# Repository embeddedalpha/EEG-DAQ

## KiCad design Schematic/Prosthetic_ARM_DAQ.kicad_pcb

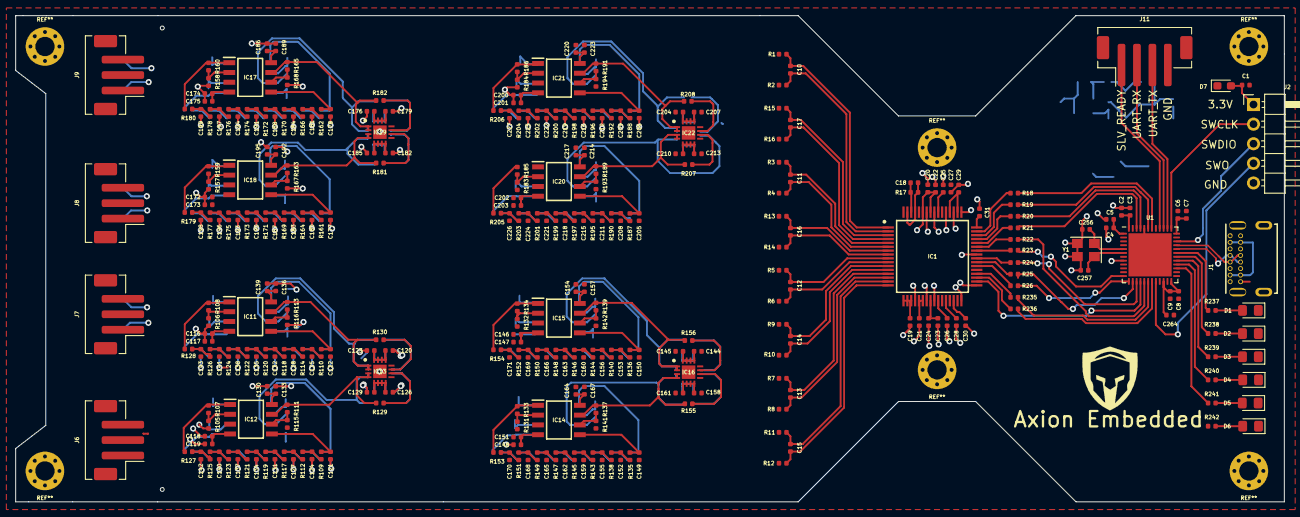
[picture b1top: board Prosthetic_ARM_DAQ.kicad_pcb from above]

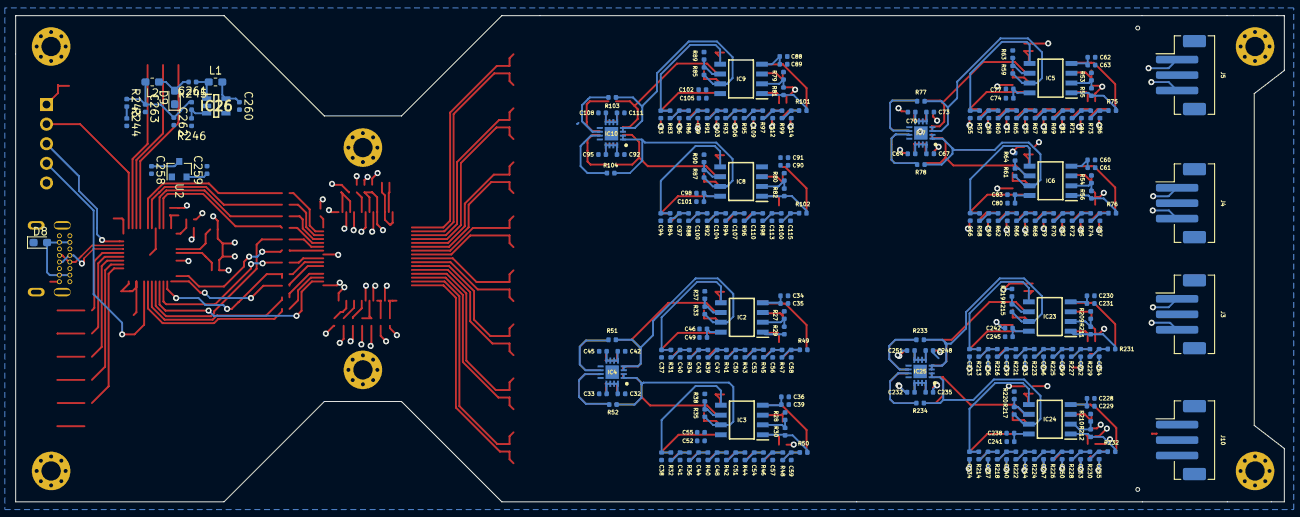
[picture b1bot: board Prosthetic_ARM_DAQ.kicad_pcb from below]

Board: 4 copper layers, 164.4 x 63.0 mm, 561 parts (248 on the bottom side), 301 nets.

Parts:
C1, C2, C4, C6, C8, C258, C259, C260, C261, C262, C263: 100U; C_0402_1005Metric
C3, C5, C7, C9, C256, C257, C264: 1N; C_0402_1005Metric
C10, C11, C12, C13, C14, C15, C16, C17, C37, C38, C40, C41, C43, C44, C47, C48, C50, C51, C53, C54, C56, C57, C58, C59, C65, C66, C68, C69, C71, C72, C75, C76, C78, C79, C81, C82, C84, C85, C86, C87, C93, C94, C96, C97, C99, C100, C103, C104, C106, C107, C109, C110, C112, C113, C114, C115, C121, C122, C124, C125, C127, C128, C131, C132, C134, C135, C137, C138, C140, C141, C142, C143, C149, C150, C152, C153, C155, C156, C159, C160, C162, C163, C165, C166, C168, C169, C170, C171, C177, C178, C180, C181, C183, C184, C187, C188, C190, C191, C193, C194, C196, C197, C198, C199, C205, C206, C208, C209, C211, C212, C215, C216, C218, C219, C221, C222, C224, C225, C226, C227, C233, C234, C236, C237, C239, C240, C243, C244, C246, C247, C249, C250, C252, C253, C254, C255: C_Small; C_0402_1005Metric
C18, C19, C20, C21, C22, C23, C24, C25, C26, C27, C28, C29, C30, C31: 1U; C_0402_1005Metric
C32, C34, C36, C42, C46, C52, C60, C62, C64, C70, C74, C80, C88, C90, C92, C98, C102, C108, C116, C118, C120, C126, C130, C136, C144, C146, C148, C154, C158, C164, C172, C174, C176, C182, C186, C192, C200, C202, C204, C210, C214, C220, C228, C230, C232, C238, C242, C248: 0.1U; C_0402_1005Metric
C33, C35, C39, C45, C49, C55, C61, C63, C67, C73, C77, C83, C89, C91, C95, C101, C105, C111, C117, C119, C123, C129, C133, C139, C145, C147, C151, C157, C161, C167, C173, C175, C179, C185, C189, C195, C201, C203, C207, C213, C217, C223, C229, C231, C235, C241, C245, C251: 10U; C_0402_1005Metric
D1, D2, D3, D4, D5, D6: LED; LED_0805_2012Metric_Pad1.15x1.40mm_HandSolder
D7, D8, D9: D_Small; D_0603_1608Metric_Pad1.05x0.95mm_HandSolder
IC1: ADS1299-4PAGR; QFP50P1200X1200X120-64N
IC2, IC3, IC5, IC6, IC8, IC9, IC11, IC12, IC14, IC15, IC17, IC18, IC20, IC21, IC23, IC24: ADA4075-2ARZ; SOIC127P600X175-8N
IC4, IC7, IC10, IC13, IC16, IC19, IC22, IC25: AD8476ACPZ-WP; QFN50P300X300X80-17N-D
IC26: LM2611AMF; SOT95P280X145-5N
J1: USB4085-GF-A_REVA; USB_C_New
J2: Conn_01x05; PinHeader_1x05_P2.54mm_Horizontal
J3, J4, J5, J6, J7, J8, J9, J10: Conn_01x03; JST_PH_B3B-PH-SM4-TB_1x03-1MP_P2.00mm_Vertical
J11: Conn_01x04; JST_PH_B4B-PH-SM4-TB_1x04-1MP_P2.00mm_Vertical
L1, L2: L_Small; L_0603_1608Metric_Pad1.05x0.95mm_HandSolder
R1, R2, R3, R4, R5, R6, R7, R8, R9, R10, R11, R12, R13, R14, R15, R16, R17, R18, R19, R20, R21, R22, R23, R24, R25, R26, R27, R28, R29, R30, R31, R32, R33, R34, R35, R36, R37, R38, R39, R40, R41, R42, R43, R44, R45, R46, R47, R48, R49, R50, R51, R52, R53, R54, R55, R56, R57, R58, R59, R60, R61, R62, R63, R64, R65, R66, R67, R68, R69, R70, R71, R72, R73, R74, R75, R76, R77, R78, R79, R80, R81, R82, R83, R84, R85, R86, R87, R88, R89, R90, R91, R92, R93, R94, R95, R96, R97, R98, R99, R100, R101, R102, R103, R104, R105, R106, R107, R108, R109, R110, R111, R112, R113, R114, R115, R116, R117, R118, R119, R120, R121, R122, R123, R124, R125, R126, R127, R128, R129, R130, R131, R132, R133, R134, R135, R136, R137, R138, R139, R140, R141, R142, R143, R144, R145, R146, R147, R148, R149, R150, R151, R152, R153, R154, R155, R156, R157, R158, R159, R160, R161, R162, R163, R164, R165, R166, R167, R168, R169, R170, R171, R172, R173, R174, R175, R176, R177, R178, R179, R180, R181, R182, R183, R184, R185, R186, R187, R188, R189, R190, R191, R192, R193, R194, R195, R196, R197, R198, R199, R200, R201, R202, R203, R204, R205, R206, R207, R208, R209, R210, R211, R212, R213, R214, R215, R216, R217, R218, R219, R220, R221, R222, R223, R224, R225, R226, R227, R228, R229, R230, R231, R232, R233, R234, R235, R236, R237, R238, R239, R240, R241, R242, R243, R244, R245, R246: R_Small; R_0402_1005Metric
U1: STM32F411CEUx; QFN-48-1EP_7x7mm_P0.5mm_EP5.6x5.6mm
U2: AP2127N-3.3; SOT-23
Y1: Crystal_GND23; Crystal_SMD_TXC_7M-4Pin_3.2x2.5mm

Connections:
+3V3: C2.1, C3.1, C4.1, C5.1, C6.1, C7.1, C8.1, C9.1, C19.1, C20.1, C21.2, C22.1, C27.1, C29.2, C31.1, C42.1, C45.1, C46.1, C49.1, C52.1, C55.1, C70.1, C73.1, C74.1, C77.1, C80.1, C83.1, C98.1, C101.1, C102.1, C105.1, C108.1, C111.1, C126.1, C129.1, C130.1, C133.1, C136.1, C139.1, C154.1, C157.1, C158.1, C161.1, C164.1, C167.1, C182.1, C185.1, C186.1, C189.1, C192.1, C195.1, C210.1, C213.1, C214.1, C217.1, C220.1, C223.1, C238.1, C241.1, C242.1, C245.1, C248.1, C251.1, C259.1, C264.2, IC1.17, IC1.18, IC1.19, IC1.21, IC1.22, IC1.48, IC1.50, IC1.52, IC1.54, IC1.57, IC1.59, IC2.8, IC3.8, IC4.5, IC4.6, IC4.7, IC4.8, IC5.8, IC6.8, IC7.5, IC7.6, IC7.7, IC7.8, IC8.8, IC9.8, IC10.5, IC10.6, IC10.7, IC10.8, IC11.8, IC12.8, IC13.5, IC13.6, IC13.7, IC13.8, IC14.8, IC15.8, IC16.5, IC16.6, IC16.7, IC16.8, IC17.8, IC18.8, IC19.5, IC19.6, IC19.7, IC19.8, IC20.8, IC21.8, IC22.5, IC22.6, IC22.7, IC22.8, IC23.8, IC24.8, IC25.5, IC25.6, IC25.7, IC25.8, R242.1, U1.1, U1.7, U1.9, U1.22, U1.24, U1.36, U1.48, U2.2
-3V3: C32.1, C33.1, C34.1, C35.1, C36.1, C39.1, C60.1, C61.1, C62.1, C63.1, C64.1, C67.1, C88.1, C89.1, C90.1, C91.1, C92.1, C95.1, C116.1, C117.1, C118.1, C119.1, C120.1, C123.1, C144.1, C145.1, C146.1, C147.1, C148.1, C151.1, C172.1, C173.1, C174.1, C175.1, C176.1, C179.1, C200.1, C201.1, C202.1, C203.1, C204.1, C207.1, C228.1, C229.1, C230.1, C231.1, C232.1, C235.1, IC2.4, IC3.4, IC4.13, IC4.14, IC4.15, IC4.16, IC5.4, IC6.4, IC7.13, IC7.14, IC7.15, IC7.16, IC8.4, IC9.4, IC10.13, IC10.14, IC10.15, IC10.16, IC11.4, IC12.4, IC13.13, IC13.14, IC13.15, IC13.16, IC14.4, IC15.4, IC16.13, IC16.14, IC16.15, IC16.16, IC17.4, IC18.4, IC19.13, IC19.14, IC19.15, IC19.16, IC20.4, IC21.4, IC22.13, IC22.14, IC22.15, IC22.16, IC23.4, IC24.4, IC25.13, IC25.14, IC25.15, IC25.16, R243.2, R244.1
/Analog_AFE/sheet5F407F6A/EMG1_+: IC13.10, R12.1, R129.1
/Analog_AFE/sheet5F407F6A/EMG1_-: IC13.11, R11.2, R130.1
/Analog_AFE/sheet5F407F6A/IN1: IC12.7, IC13.3, IC13.4, R111.1, R129.2
/Analog_AFE/sheet5F407F6A/IN2: IC11.7, IC13.1, IC13.2, R113.1, R130.2
/Analog_AFE/sheet5F407F6B/EMG2_+: IC16.10, R10.1, R155.1
/Analog_AFE/sheet5F407F6B/EMG2_-: IC16.11, R9.2, R156.1
/Analog_AFE/sheet5F407F6B/IN1: IC14.7, IC16.3, IC16.4, R137.1, R155.2
/Analog_AFE/sheet5F407F6B/IN2: IC15.7, IC16.1, IC16.2, R139.1, R156.2
/Analog_AFE/sheet5F407F6C/EMG3_+: IC19.10, R14.1, R181.1
/Analog_AFE/sheet5F407F6C/EMG3_-: IC19.11, R13.2, R182.1
/Analog_AFE/sheet5F407F6C/IN1: IC18.7, IC19.3, IC19.4, R163.1, R181.2
/Analog_AFE/sheet5F407F6C/IN2: IC17.7, IC19.1, IC19.2, R165.1, R182.2
/Analog_AFE/sheet5F407F6D/EMG4_+: IC22.10, R16.1, R207.1
/Analog_AFE/sheet5F407F6D/EMG4_-: IC22.11, R15.2, R208.1
/Analog_AFE/sheet5F407F6D/IN1: IC20.7, IC22.3, IC22.4, R189.1, R207.2
/Analog_AFE/sheet5F407F6D/IN2: IC21.7, IC22.1, IC22.2, R191.1, R208.2
/Analog_AFE/sheet5F407F6E/EEG1_+: IC25.10, R8.1, R233.1
/Analog_AFE/sheet5F407F6E/EEG1_-: IC25.11, R7.2, R234.1
/Analog_AFE/sheet5F407F6E/IN1: IC23.7, IC25.3, IC25.4, R215.1, R233.2
/Analog_AFE/sheet5F407F6E/IN2: IC24.7, IC25.1, IC25.2, R217.1, R234.2
/Analog_AFE/sheet5F407F67/EEG2_+: IC4.10, R6.1, R51.1
/Analog_AFE/sheet5F407F67/EEG2_-: IC4.11, R5.2, R52.1
/Analog_AFE/sheet5F407F67/IN1: IC2.7, IC4.3, IC4.4, R33.1, R51.2
/Analog_AFE/sheet5F407F67/IN2: IC3.7, IC4.1, IC4.2, R35.1, R52.2
/Analog_AFE/sheet5F407F68/EEG3_+: IC7.10, R4.1, R77.1
/Analog_AFE/sheet5F407F68/EEG3_-: IC7.11, R3.2, R78.1
/Analog_AFE/sheet5F407F68/IN1: IC5.7, IC7.3, IC7.4, R59.1, R77.2
/Analog_AFE/sheet5F407F68/IN2: IC6.7, IC7.1, IC7.2, R61.1, R78.2
/Analog_AFE/sheet5F407F69/EEG4_+: IC10.10, R2.1, R103.1
/Analog_AFE/sheet5F407F69/EEG4_-: IC10.11, R1.2, R104.1
/Analog_AFE/sheet5F407F69/IN1: IC9.7, IC10.3, IC10.4, R85.1, R103.2
/Analog_AFE/sheet5F407F69/IN2: IC8.7, IC10.1, IC10.2, R87.1, R104.2
DIN: IC1.34, U1.16
DN_N: J1.A7, J1.B7, U1.32
DN_P: J1.A6, J1.B6, U1.33
DOUT: R22.1, U1.17
DRDY: R18.1, U1.42
GND: C1.2, C2.2, C3.2, C4.2, C5.2, C6.2, C7.2, C8.2, C9.2, C19.2, C20.2, C21.1, C22.2, C23.1, C24.1, C25.1, C26.1, C27.2, C28.1, C29.1, C30.1, C31.2, C32.2, C33.2, C34.2, C35.2, C36.2, C37.2, C38.2, C39.2, C40.2, C41.2, C42.2, C43.2, C44.2, C45.2, C46.2, C47.2, C48.2, C49.2, C50.2, C51.2, C52.2, C53.2, C54.2, C55.2, C56.2, C57.2, C58.2, C59.2, C60.2, C61.2, C62.2, C63.2, C64.2, C65.2, C66.2, C67.2, C68.2, C69.2, C70.2, C71.2, C72.2, C73.2, C74.2, C75.2, C76.2, C77.2, C78.2, C79.2, C80.2, C81.2, C82.2, C83.2, C84.2, C85.2, C86.2, C87.2, C88.2, C89.2, C90.2, C91.2, C92.2, C93.2, C94.2, C95.2, C96.2, C97.2, C98.2, C99.2, C100.2, C101.2, C102.2, C103.2, C104.2, C105.2, C106.2, C107.2, C108.2, C109.2, C110.2, C111.2, C112.2, C113.2, C114.2, C115.2, C116.2, C117.2, C118.2, C119.2, C120.2, C121.2, C122.2, C123.2, C124.2, C125.2, C126.2, C127.2, C128.2, C129.2, C130.2, C131.2, C132.2, C133.2, C134.2, C135.2, C136.2, C137.2, C138.2, C139.2, C140.2, C141.2, C142.2, C143.2, C144.2, C145.2, C146.2, C147.2, C148.2, C149.2, C150.2, C151.2, C152.2, C153.2, C154.2, C155.2, C156.2, C157.2, C158.2, C159.2, C160.2, C161.2, C162.2, C163.2, C164.2, C165.2, C166.2, C167.2, C168.2, C169.2, C170.2, C171.2, C172.2, C173.2, C174.2, C175.2, C176.2, C177.2, C178.2, C179.2, C180.2, C181.2, C182.2, C183.2, C184.2, C185.2, C186.2, C187.2, C188.2, C189.2, C190.2, C191.2, C192.2, C193.2, C194.2, C195.2, C196.2, C197.2, C198.2, C199.2, C200.2, C201.2, C202.2, C203.2, C204.2, C205.2, C206.2, C207.2, C208.2, C209.2, C210.2, C211.2, C212.2, C213.2, C214.2, C215.2, C216.2, C217.2, C218.2, C219.2, C220.2, C221.2, C222.2, C223.2, C224.2, C225.2, C226.2, C227.2, C228.2, C229.2, C230.2, C231.2, C232.2, C233.2, C234.2, C235.2, C236.2, C237.2, C238.2, C239.2, C240.2, C241.2, C242.2, C243.2, C244.2, C245.2, C246.2, C247.2, C248.2, C249.2, C250.2, C251.2, C252.2, C253.2, C254.2, C255.2, C256.1, C257.2, C258.2, C259.2, C260.2, C263.2, C264.1, D1.1, D2.1, D3.1, D4.1, D5.1, D6.1, D9.1, IC1.20, IC1.23, IC1.25, IC1.32, IC1.33, IC1.41, IC1.49, IC1.51, IC1.53, IC1.56, IC1.58, IC4.17, IC7.17, IC10.17, IC13.17, IC16.17, IC19.17, IC22.17, IC25.17, IC26.2, J1.A1, J1.A12, J1.B1, J1.B12, J1.P1, J1.P2, J1.P3, J1.P4, J2.5, J3.2, J4.2, J5.2, J6.2, J7.2, J8.2, J9.2, J10.2, J11.4, R27.2, R28.2, R37.2, R38.2, R53.2, R54.2, R63.2, R64.2, R79.2, R80.2, R89.2, R90.2, R105.2, R106.2, R115.2, R116.2, R131.2, R132.2, R141.2, R142.2, R157.2, R158.2, R167.2, R168.2, R183.2, R184.2, R193.2, R194.2, R209.2, R210.2, R219.2, R220.2, R244.2, R246.2, U1.8, U1.23, U1.35, U1.44, U1.47, U1.49, U2.1, Y1.2, Y1.3
GPIO1: R23.1, U1.12
GPIO2: R21.1, U1.46
GPIO3: R20.1, U1.45
GPIO4: R19.1, U1.43
LED1: R237.1, U1.31
LED2: R238.1, U1.30
LED3: R239.1, U1.29
LED4: R240.1, U1.28
LED5: R241.1, U1.27
NFB: C262.2, IC26.3, R245.2, R246.1
unnamed: C1.1, D7.2, J2.1
unnamed: C10.1, IC1.1, R1.1
unnamed: C10.2, IC1.2, R2.2
unnamed: C11.1, IC1.5, R3.1
unnamed: C11.2, IC1.6, R4.2
unnamed: C12.1, IC1.9, R5.1
unnamed: C12.2, IC1.10, R6.2
unnamed: C13.1, IC1.13, R7.1
unnamed: C13.2, IC1.14, R8.2
unnamed: C14.1, IC1.11, R9.1
unnamed: C14.2, IC1.12, R10.2
unnamed: C15.1, IC1.15, R11.1
unnamed: C15.2, IC1.16, R12.2
unnamed: C16.1, IC1.7, R13.1
unnamed: C16.2, IC1.8, R14.2
unnamed: C17.1, IC1.3, R15.1
unnamed: C17.2, IC1.4, R16.2
unnamed: C18.1, IC1.62, R17.1
unnamed: C18.2, IC1.61, IC1.63, R17.2
unnamed: C23.2, C24.2, IC1.24
unnamed: C25.2, IC1.55
unnamed: C26.2, IC1.26
unnamed: C28.2, IC1.28
unnamed: C30.2, IC1.30
unnamed: C37.1, IC2.5, R31.1
unnamed: C38.1, IC3.5, R32.1
unnamed: C40.1, R31.2, R34.1
unnamed: C41.1, R32.2, R36.1
unnamed: C43.1, R34.2, R39.1
unnamed: C44.1, R36.2, R40.1
unnamed: C47.1, R39.2, R41.1
unnamed: C48.1, R40.2, R42.1
unnamed: C50.1, R41.2, R43.1
unnamed: C51.1, R42.2, R44.1
unnamed: C53.1, R43.2, R45.1
unnamed: C54.1, R44.2, R46.1
unnamed: C56.1, R45.2, R47.1
unnamed: C57.1, R46.2, R48.1
unnamed: C58.1, R47.2, R49.1
unnamed: C59.1, R48.2, R50.1
unnamed: C65.1, IC5.5, R57.1
unnamed: C66.1, IC6.5, R58.1
unnamed: C68.1, R57.2, R60.1
unnamed: C69.1, R58.2, R62.1
unnamed: C71.1, R60.2, R65.1
unnamed: C72.1, R62.2, R66.1
unnamed: C75.1, R65.2, R67.1
unnamed: C76.1, R66.2, R68.1
unnamed: C78.1, R67.2, R69.1
unnamed: C79.1, R68.2, R70.1
unnamed: C81.1, R69.2, R71.1
unnamed: C82.1, R70.2, R72.1
unnamed: C84.1, R71.2, R73.1
unnamed: C85.1, R72.2, R74.1
unnamed: C86.1, R73.2, R75.1
unnamed: C87.1, R74.2, R76.1
unnamed: C93.1, IC9.5, R83.1
unnamed: C94.1, IC8.5, R84.1
unnamed: C96.1, R83.2, R86.1
unnamed: C97.1, R84.2, R88.1
unnamed: C99.1, R86.2, R91.1
unnamed: C100.1, R88.2, R92.1
unnamed: C103.1, R91.2, R93.1
unnamed: C104.1, R92.2, R94.1
unnamed: C106.1, R93.2, R95.1
unnamed: C107.1, R94.2, R96.1
unnamed: C109.1, R95.2, R97.1
unnamed: C110.1, R96.2, R98.1
unnamed: C112.1, R97.2, R99.1
unnamed: C113.1, R98.2, R100.1
unnamed: C114.1, R99.2, R101.1
unnamed: C115.1, R100.2, R102.1
unnamed: C121.1, IC12.5, R109.1
unnamed: C122.1, IC11.5, R110.1
unnamed: C124.1, R109.2, R112.1
unnamed: C125.1, R110.2, R114.1
unnamed: C127.1, R112.2, R117.1
unnamed: C128.1, R114.2, R118.1
unnamed: C131.1, R117.2, R119.1
unnamed: C132.1, R118.2, R120.1
unnamed: C134.1, R119.2, R121.1
unnamed: C135.1, R120.2, R122.1
unnamed: C137.1, R121.2, R123.1
unnamed: C138.1, R122.2, R124.1
unnamed: C140.1, R123.2, R125.1
unnamed: C141.1, R124.2, R126.1
unnamed: C142.1, R125.2, R127.1
unnamed: C143.1, R126.2, R128.1
unnamed: C149.1, IC14.5, R135.1
unnamed: C150.1, IC15.5, R136.1
unnamed: C152.1, R135.2, R138.1
unnamed: C153.1, R136.2, R140.1
unnamed: C155.1, R138.2, R143.1
unnamed: C156.1, R140.2, R144.1
unnamed: C159.1, R143.2, R145.1
unnamed: C160.1, R144.2, R146.1
unnamed: C162.1, R145.2, R147.1
unnamed: C163.1, R146.2, R148.1
unnamed: C165.1, R147.2, R149.1
unnamed: C166.1, R148.2, R150.1
unnamed: C168.1, R149.2, R151.1
unnamed: C169.1, R150.2, R152.1
unnamed: C170.1, R151.2, R153.1
unnamed: C171.1, R152.2, R154.1
unnamed: C177.1, IC18.5, R161.1
unnamed: C178.1, IC17.5, R162.1
unnamed: C180.1, R161.2, R164.1
unnamed: C181.1, R162.2, R166.1
unnamed: C183.1, R164.2, R169.1
unnamed: C184.1, R166.2, R170.1
unnamed: C187.1, R169.2, R171.1
unnamed: C188.1, R170.2, R172.1
unnamed: C190.1, R171.2, R173.1
unnamed: C191.1, R172.2, R174.1
unnamed: C193.1, R173.2, R175.1
unnamed: C194.1, R174.2, R176.1
unnamed: C196.1, R175.2, R177.1
unnamed: C197.1, R176.2, R178.1
unnamed: C198.1, R177.2, R179.1
unnamed: C199.1, R178.2, R180.1
unnamed: C205.1, IC20.5, R187.1
unnamed: C206.1, IC21.5, R188.1
unnamed: C208.1, R187.2, R190.1
unnamed: C209.1, R188.2, R192.1
unnamed: C211.1, R190.2, R195.1
unnamed: C212.1, R192.2, R196.1
unnamed: C215.1, R195.2, R197.1
unnamed: C216.1, R196.2, R198.1
unnamed: C218.1, R197.2, R199.1
unnamed: C219.1, R198.2, R200.1
unnamed: C221.1, R199.2, R201.1
unnamed: C222.1, R200.2, R202.1
unnamed: C224.1, R201.2, R203.1
unnamed: C225.1, R202.2, R204.1
unnamed: C226.1, R203.2, R205.1
unnamed: C227.1, R204.2, R206.1
unnamed: C233.1, IC23.5, R213.1
unnamed: C234.1, IC24.5, R214.1
unnamed: C236.1, R213.2, R216.1
unnamed: C237.1, R214.2, R218.1
unnamed: C239.1, R216.2, R221.1
unnamed: C240.1, R218.2, R222.1
unnamed: C243.1, R221.2, R223.1
unnamed: C244.1, R222.2, R224.1
unnamed: C246.1, R223.2, R225.1
unnamed: C247.1, R224.2, R226.1
unnamed: C249.1, R225.2, R227.1
unnamed: C250.1, R226.2, R228.1
unnamed: C252.1, R227.2, R229.1
unnamed: C253.1, R228.2, R230.1
unnamed: C254.1, R229.2, R231.1
unnamed: C255.1, R230.2, R232.1
unnamed: C261.2, D9.2, L2.1
unnamed: D1.2, R237.2
unnamed: D2.2, R238.2
unnamed: D3.2, R239.2
unnamed: D4.2, R240.2
unnamed: D5.2, R241.2
unnamed: D6.2, R242.2
unnamed: D8.2, J1.A4, J1.A9, J1.B4, J1.B9
unnamed: IC1.35, R236.2
unnamed: IC1.36, R235.2
unnamed: IC1.38, R26.2
unnamed: IC1.39, R25.2
unnamed: IC1.40, R24.2
unnamed: IC1.42, R23.2
unnamed: IC1.43, R22.2
unnamed: IC1.44, R21.2
unnamed: IC1.45, R20.2
unnamed: IC1.46, R19.2
unnamed: IC1.47, R18.2
unnamed: IC2.1, R29.1, R49.2
unnamed: IC2.2, R27.1, R29.2
unnamed: IC2.3, J3.1
unnamed: IC2.6, R33.2, R37.1
unnamed: IC3.1, R30.1, R50.2
unnamed: IC3.2, R28.1, R30.2
unnamed: IC3.3, J3.3
unnamed: IC3.6, R35.2, R38.1
unnamed: IC5.1, R55.1, R75.2
unnamed: IC5.2, R53.1, R55.2
unnamed: IC5.3, J4.1
unnamed: IC5.6, R59.2, R63.1
unnamed: IC6.1, R56.1, R76.2
unnamed: IC6.2, R54.1, R56.2
unnamed: IC6.3, J4.3
unnamed: IC6.6, R61.2, R64.1
unnamed: IC8.1, R82.1, R102.2
unnamed: IC8.2, R80.1, R82.2
unnamed: IC8.3, J5.3
unnamed: IC8.6, R87.2, R90.1
unnamed: IC9.1, R81.1, R101.2
unnamed: IC9.2, R79.1, R81.2
unnamed: IC9.3, J5.1
unnamed: IC9.6, R85.2, R89.1
unnamed: IC11.1, R108.1, R128.2
unnamed: IC11.2, R106.1, R108.2
unnamed: IC11.3, J6.3
unnamed: IC11.6, R113.2, R116.1
unnamed: IC12.1, R107.1, R127.2
unnamed: IC12.2, R105.1, R107.2
unnamed: IC12.3, J6.1
unnamed: IC12.6, R111.2, R115.1
unnamed: IC14.1, R133.1, R153.2
unnamed: IC14.2, R131.1, R133.2
unnamed: IC14.3, J7.1
unnamed: IC14.6, R137.2, R141.1
unnamed: IC15.1, R134.1, R154.2
unnamed: IC15.2, R132.1, R134.2
unnamed: IC15.3, J7.3
unnamed: IC15.6, R139.2, R142.1
unnamed: IC17.1, R160.1, R180.2
unnamed: IC17.2, R158.1, R160.2
unnamed: IC17.3, J8.3
unnamed: IC17.6, R165.2, R168.1
unnamed: IC18.1, R159.1, R179.2
unnamed: IC18.2, R157.1, R159.2
unnamed: IC18.3, J8.1
unnamed: IC18.6, R163.2, R167.1
unnamed: IC20.1, R185.1, R205.2
unnamed: IC20.2, R183.1, R185.2
unnamed: IC20.3, J9.1
unnamed: IC20.6, R189.2, R193.1
unnamed: IC21.1, R186.1, R206.2
unnamed: IC21.2, R184.1, R186.2
unnamed: IC21.3, J9.3
unnamed: IC21.6, R191.2, R194.1
unnamed: IC23.1, R211.1, R231.2
unnamed: IC23.2, R209.1, R211.2
unnamed: IC23.3, J10.1
unnamed: IC23.6, R215.2, R219.1
unnamed: IC24.1, R212.1, R232.2
unnamed: IC24.2, R210.1, R212.2
unnamed: IC24.3, J10.3
unnamed: IC24.6, R217.2, R220.1
O: C262.1, C263.1, L2.2, R243.1, R245.1
OSC_IN: C256.2, U1.5, Y1.1
OSC_OUT: C257.1, U1.6, Y1.4
SCLK: R24.1, U1.15
SLAVE_READY: J11.1, U1.40
START: R26.1, U1.13
SW: C261.1, IC26.1, L1.2
SWCLK: J2.2, U1.37
SWDIO: J2.3, U1.34
SWO: J2.4, U1.20
USART_RX: J11.2, U1.39
USART_TX: J11.3, U1.38
VDD: C258.1, C260.1, D7.1, D8.1, IC26.4, IC26.5, L1.1, U2.3
nCS: R25.1, U1.14
nPWDN: R236.1, U1.19
nRESET: R235.1, U1.18

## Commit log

2020-08-16 Create txt
